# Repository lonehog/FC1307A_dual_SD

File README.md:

# FC1307A Dual SD Card Adapter

Open-hardware reverse engineering of the iPod dual SD card adapter built around the **FC1307A** controller — schematics, PCB design and Gerbers, free to use and adapt for your own projects.(under making)

<p align="center">
  
  <br />
  <em>Source adapter (front &amp; back), sourced from AliExpress</em>
</p>

---

## Project status

- [x] Schematics based on the reference Reddit post
- [ ] Correction and revision of the initial schematics against the real hardware
- [ ] PCB design in KiCad
- [ ] Assembly and testing with iPod Classic 5th gen and 7th gen
- [ ] Final release of Gerber files

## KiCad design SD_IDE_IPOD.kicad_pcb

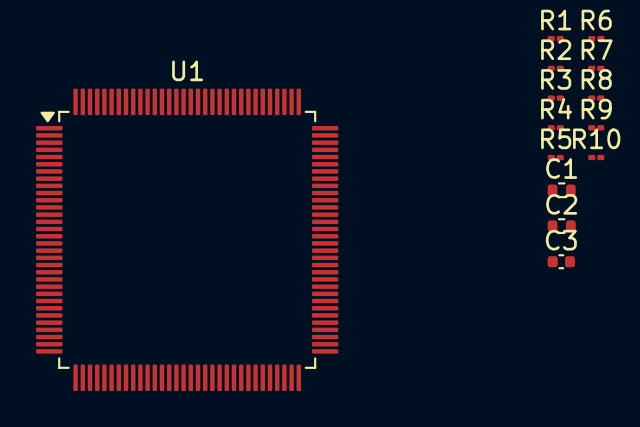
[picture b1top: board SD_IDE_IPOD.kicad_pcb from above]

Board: 2 copper layers, 14 parts (0 on the bottom side), 11 nets, no tracks yet.

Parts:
C1, C2: 1uF; R_0402_1005Metric
C3: 100nF; C_0402_1005Metric
R1, R2, R3, R4, R5, R6, R7, R8, R9, R10: 10k; R_01005_0402Metric
U1: FC1307A; LQFP-128_14x14mm_P0.4mm

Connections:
/SD0_CMD: R3.2, U1.115 (SD0_CLK)
/SD0_DAT0: R4.2, U1.114 (SD0_DAT0)
/SD0_DAT1: R5.2, U1.113 (SD0_DAT1), U1.116 (SD0_CMD)
/SD0_DAT2: R1.2, U1.121 (SD0_DAT2)
/SD0_DAT3: R2.2, U1.120 (SD0_DAT3)
/SD1_CMD: R8.2, U1.125 (SD1_CMD)
/SD1_DAT0: R9.2, U1.123 (SD1_DAT0)
/SD1_DAT1: R10.2, U1.122 (SD1_DAT1), U1.127 (SD1_DAT2)
/SD1_DAT2: R6.2, U1.126 (SD1_DAT3)
GND: C1.2, C2.2, C3.2
VCC: C1.1, C2.1, R1.1, R2.1, R3.1, R4.1, R5.1, R6.1, R7.1, R8.1, R9.1, R10.1
